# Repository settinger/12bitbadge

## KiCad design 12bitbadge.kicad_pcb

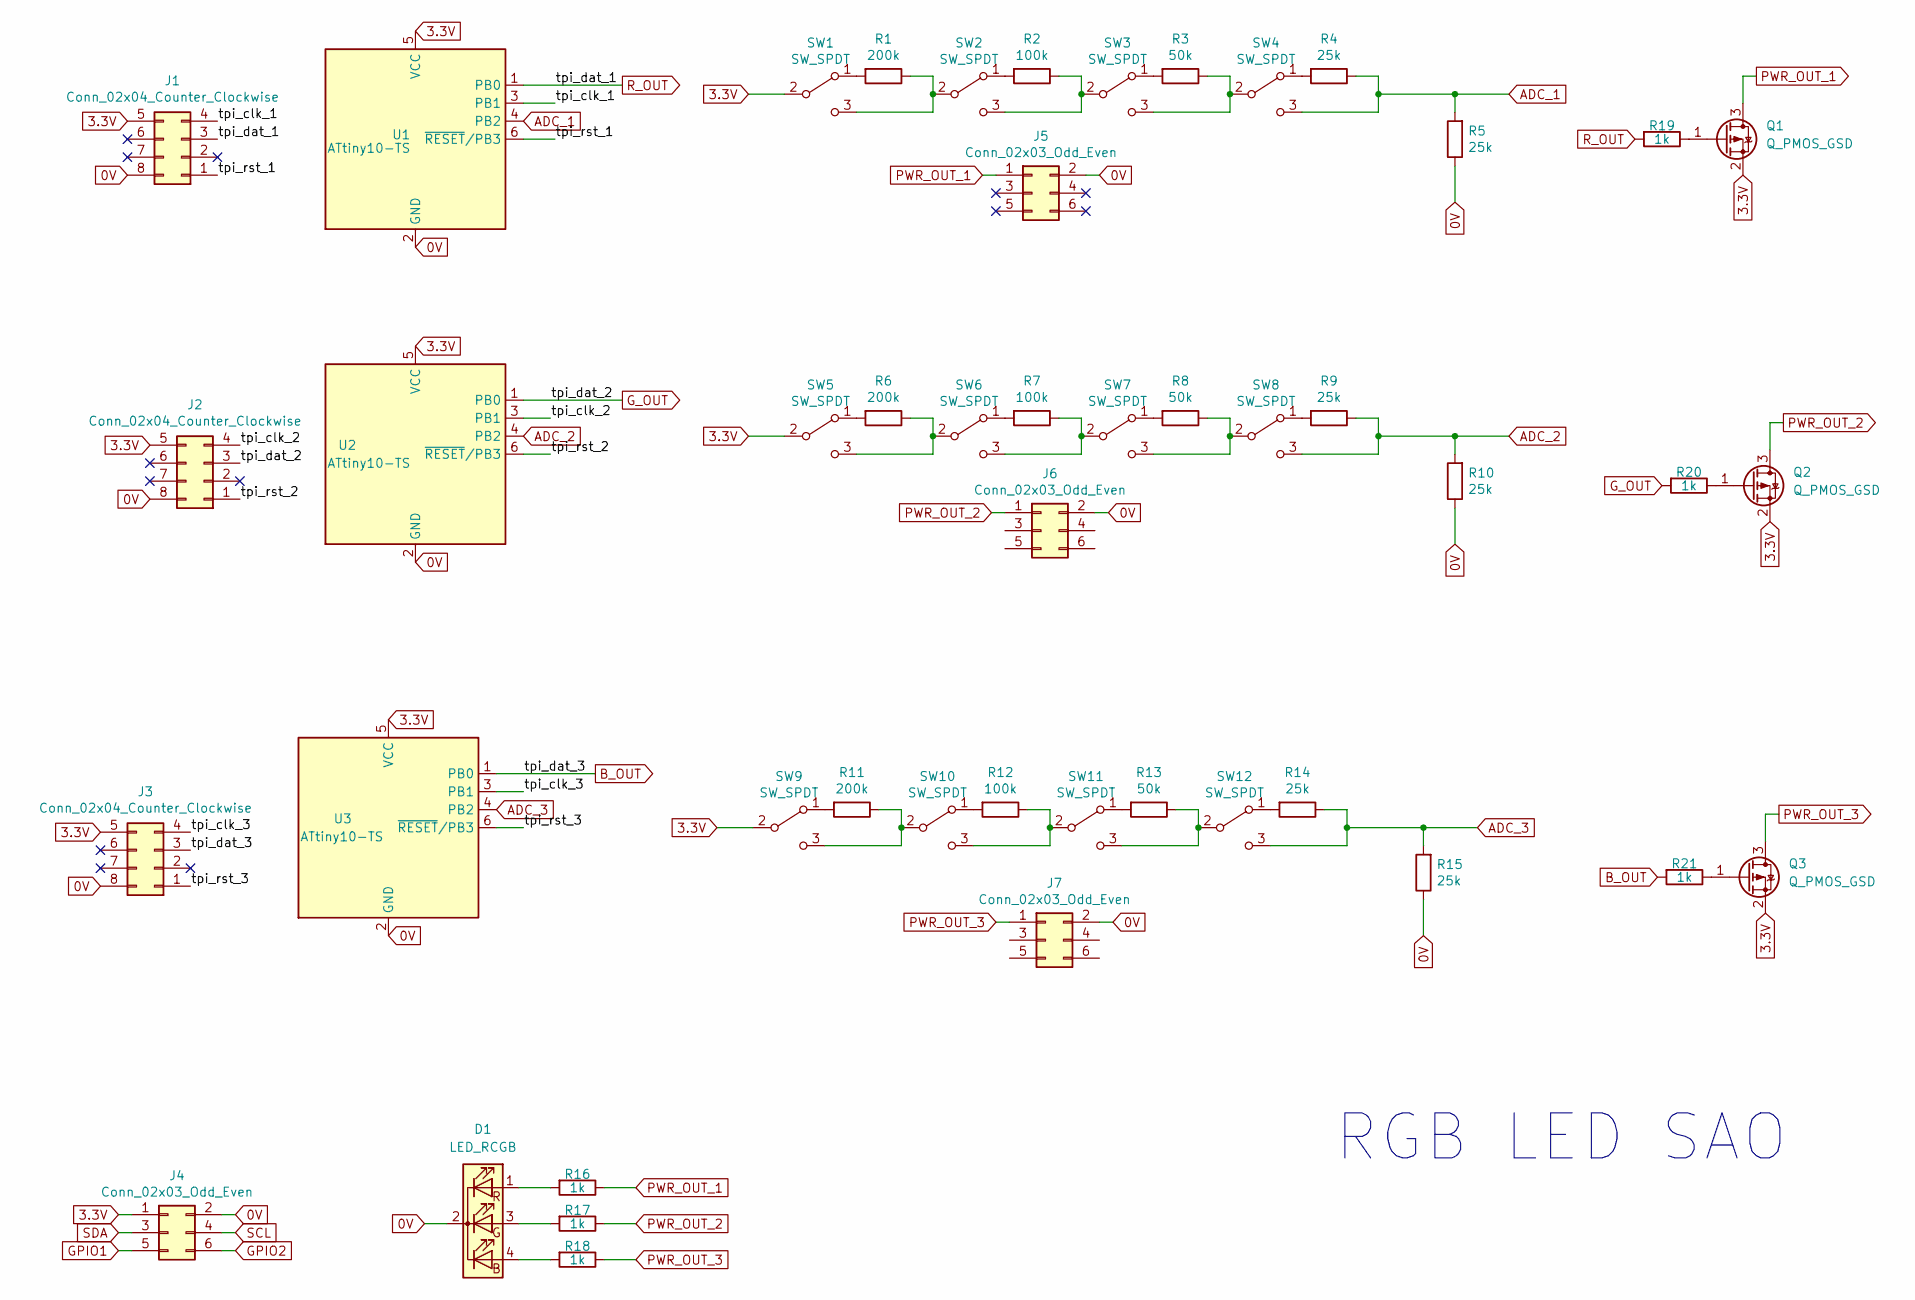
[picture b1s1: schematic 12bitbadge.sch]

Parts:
D1: LED_RCGB; LED_D5.0mm-4_RGB
J1, J2, J3: Conn_02x04_Counter_Clockwise; SOIC_clipProgSmall
J4: Conn_02x03_Odd_Even; PinHeader_2x03_P2.54mm_Vertical
J5, J6, J7: Conn_02x03_Odd_Even; PinSocket_2x03_P2.54mm_Vertical
Q1, Q2, Q3: Q_PMOS_GSD; SOT-23_Handsoldering
R1, R6, R11: 200k; R_0805_2012Metric_Pad1.15x1.40mm_HandSolder
R2, R7, R12: 100k; R_0805_2012Metric_Pad1.15x1.40mm_HandSolder
R3, R8, R13: 50k; R_0805_2012Metric_Pad1.15x1.40mm_HandSolder
R4, R5, R9, R10, R14, R15: 25k; R_0805_2012Metric_Pad1.15x1.40mm_HandSolder
R16, R17, R18, R19, R20, R21: 1k; R_0805_2012Metric_Pad1.15x1.40mm_HandSolder
SW1, SW2, SW3, SW4, SW5, SW6, SW7, SW8, SW9, SW10, SW11, SW12: SW_SPDT; SW_CuK_JS202011CQN_DPDT_Straight
U1, U2, U3: ATtiny10-TS; SOT-23-6_Handsoldering

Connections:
0V: D1.2 (K), J1.8, J2.8, J3.8, J4.2, J5.2, J6.2, J7.2, R5.1, R10.1, R15.1, U1.2 (GND), U2.2 (GND), U3.2 (GND)
3.3V: J1.5, J2.5, J3.5, J4.1, Q1.2 (S), Q2.2 (S), Q3.2 (S), SW1.2 (B), SW5.2 (B), SW9.2 (B), U1.5 (VCC), U2.5 (VCC), U3.5 (VCC)
/tpi_clk_1: J1.4, U1.3 (PB1)
/tpi_clk_2: J2.4, U2.3 (PB1)
/tpi_clk_3: J3.4, U3.3 (PB1)
/tpi_rst_1: J1.1, U1.6 (~RESET~/PB3)
/tpi_rst_2: J2.1, U2.6 (~RESET~/PB3)
/tpi_rst_3: J3.1, U3.6 (~RESET~/PB3)
ADC_1: R4.1, R5.2, SW4.3 (C), U1.4 (PB2)
ADC_2: R9.1, R10.2, SW8.3 (C), U2.4 (PB2)
ADC_3: R14.1, R15.2, SW12.3 (C), U3.4 (PB2)
B_OUT: J3.3, R21.2, U3.1 (PB0)
GPIO1: J4.5
GPIO2: J4.6
G_OUT: J2.3, R20.2, U2.1 (PB0)
unnamed: D1.1 (RA), R16.2
unnamed: D1.3 (GA), R17.2
unnamed: D1.4 (BA), R18.2
unnamed: Q1.1 (G), R19.1
unnamed: Q2.1 (G), R20.1
unnamed: Q3.1 (G), R21.1
unnamed: R1.1, SW1.3 (C), SW2.2 (B)
unnamed: R1.2, SW1.1 (A)
unnamed: R2.1, SW2.3 (C), SW3.2 (B)
unnamed: R2.2, SW2.1 (A)
unnamed: R3.1, SW3.3 (C), SW4.2 (B)
unnamed: R3.2, SW3.1 (A)
unnamed: R4.2, SW4.1 (A)
unnamed: R6.1, SW5.3 (C), SW6.2 (B)
unnamed: R6.2, SW5.1 (A)
unnamed: R7.1, SW6.3 (C), SW7.2 (B)
unnamed: R7.2, SW6.1 (A)
unnamed: R8.1, SW7.3 (C), SW8.2 (B)
unnamed: R8.2, SW7.1 (A)
unnamed: R9.2, SW8.1 (A)
unnamed: R11.1, SW9.3 (C), SW10.2 (B)
unnamed: R11.2, SW9.1 (A)
unnamed: R12.1, SW10.3 (C), SW11.2 (B)
unnamed: R12.2, SW10.1 (A)
unnamed: R13.1, SW11.3 (C), SW12.2 (B)
unnamed: R13.2, SW11.1 (A)
unnamed: R14.2, SW12.1 (A)
PWR_OUT_1: J5.1, Q1.3 (D), R16.1
PWR_OUT_2: J6.1, Q2.3 (D), R17.1
PWR_OUT_3: J7.1, Q3.3 (D), R18.1
R_OUT: J1.3, R19.2, U1.1 (PB0)
SCL: J4.4
SDA: J4.3

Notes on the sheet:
RGB LED SAO

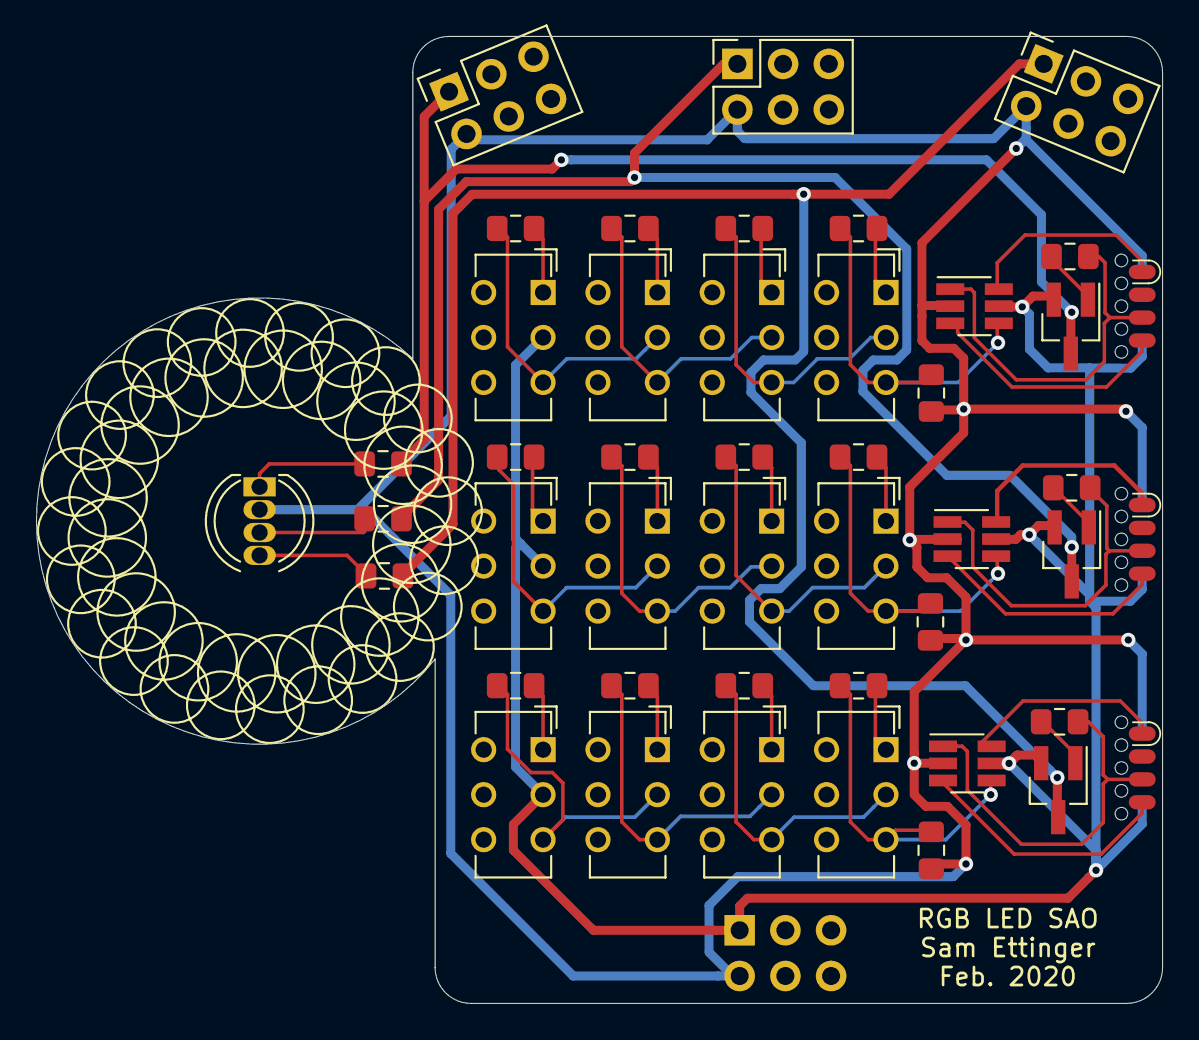
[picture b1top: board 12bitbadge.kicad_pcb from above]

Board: 2 copper layers, 62.6 x 53.7 mm, 47 parts (1 on the bottom side), 44 nets.

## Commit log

2020-01-23 Initialized project
2020-01-23 Small routing tweaks
2020-01-23 Removed errant trace above sheet
2020-01-23 Put the add-on add-onsat a more rakish angle
2020-01-23 Added gerbers
2020-01-25 Updated to hand-solderable SMD
2020-01-25 Added silkscreen rosettes
2020-01-26 Replaced switches with PWM-friendly MOSFETs
2020-01-26 Updated MOSFETs to hand-solderable pads
2020-01-26 Rounded the edges, which I always forget to do
2020-02-02 Removed copper pour, so Oshpark After Dark would look cooler
2020-02-02 Redesigning as a through-hole kit
2020-02-02 Continued work on kit version
2020-02-02 Kit version looks okay
2020-02-19 Added starter code for attiny10 firmware
2020-02-19 Added some firmware, changed the order of the resistors to minimize ADC errors
2020-02-19 Updated firmware register settings
2020-02-19 I had OC0A and OC0B mixed up
2020-02-25 added hex file
2020-03-08 Changed from common-anode RGB LED to common-cathode RGB LED
2020-03-09 Updated firmware. It works!
